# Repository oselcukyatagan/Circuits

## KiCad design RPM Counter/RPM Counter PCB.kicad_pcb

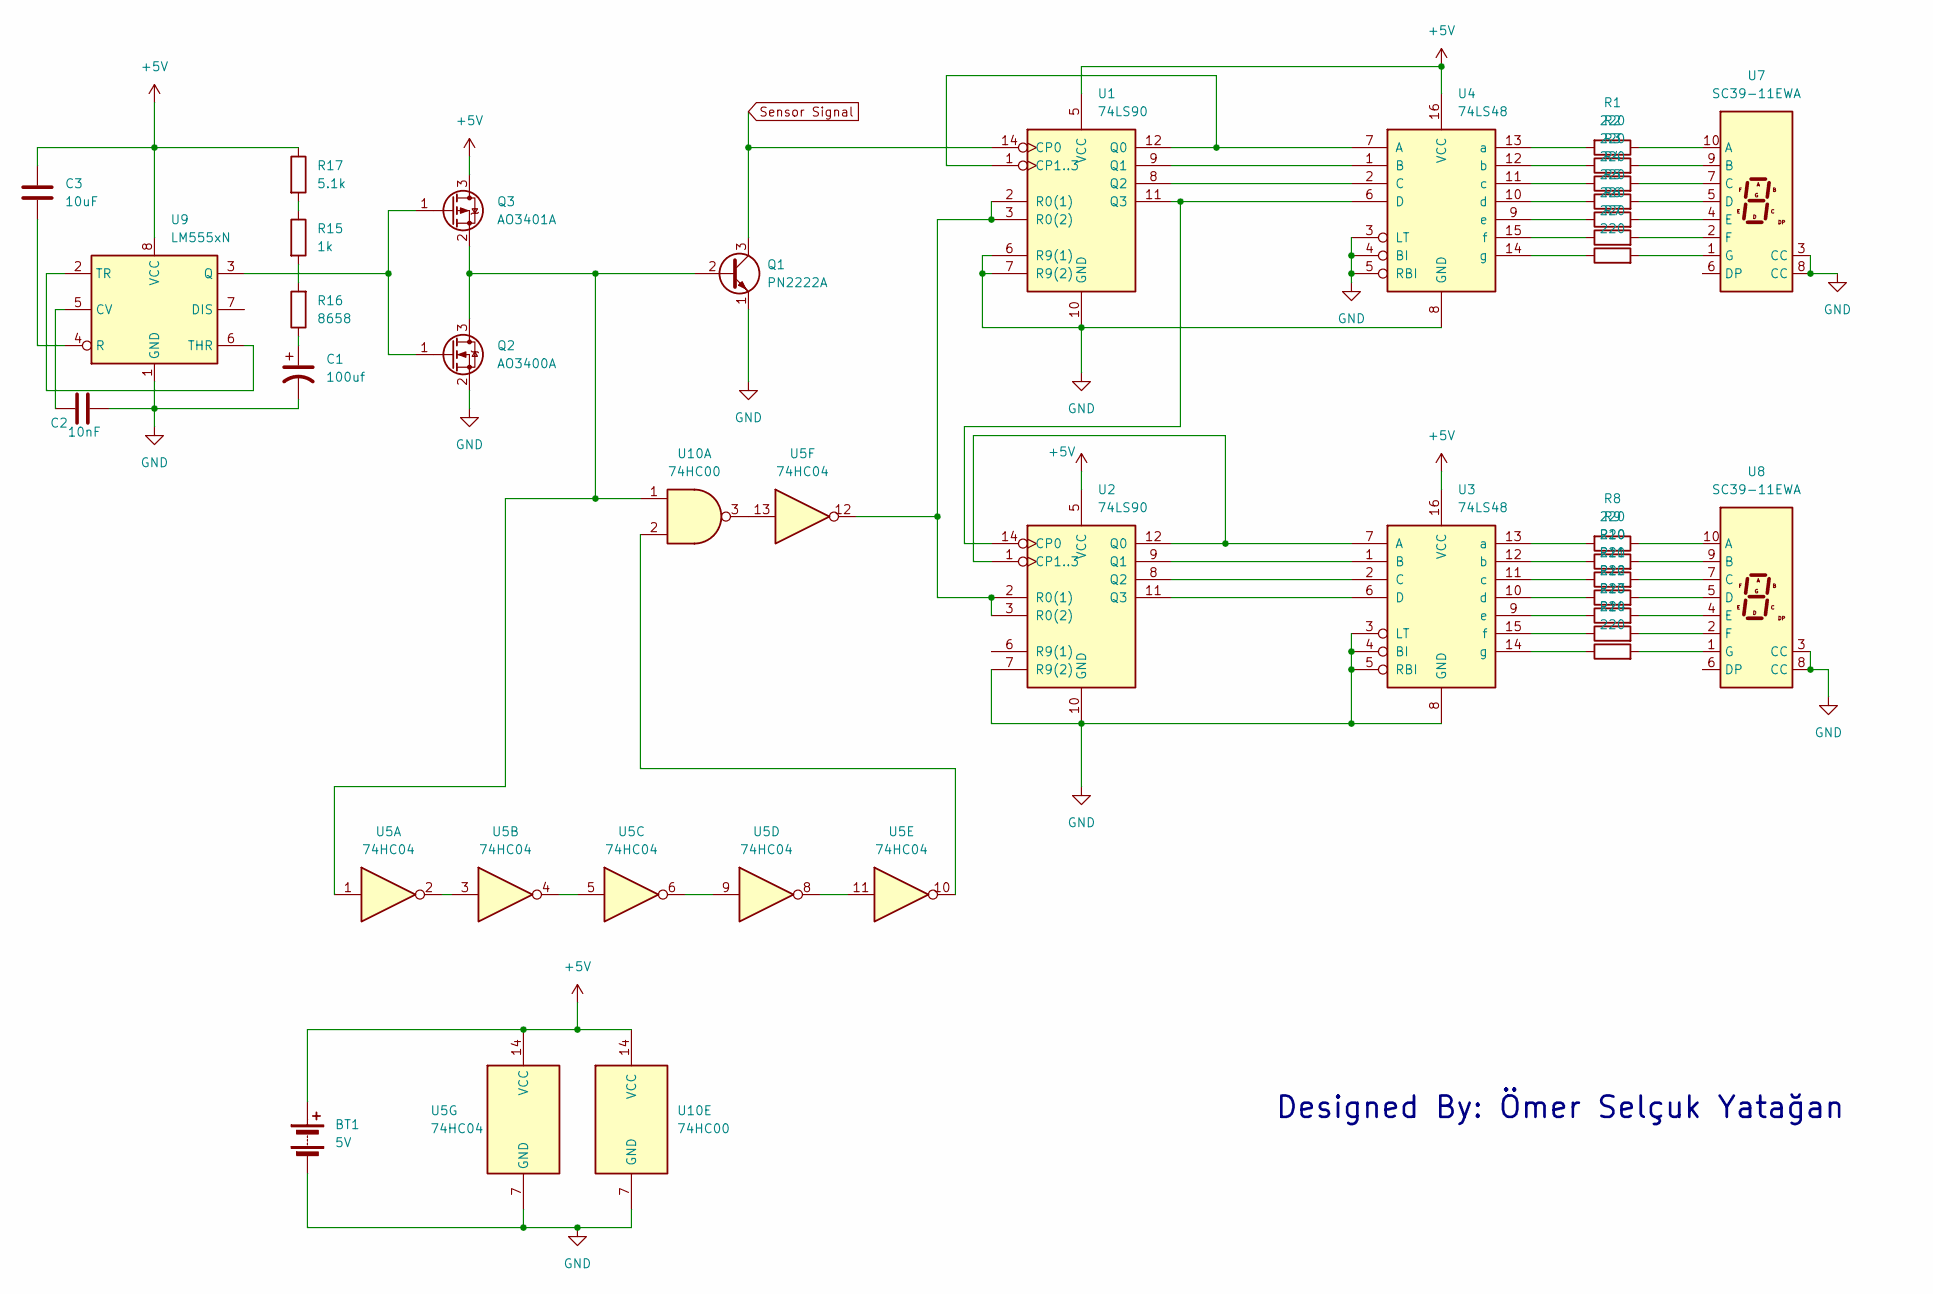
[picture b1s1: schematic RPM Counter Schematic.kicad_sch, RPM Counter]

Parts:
BT1: 5V; PinHeader_2x01_P2.54mm_Vertical
C1: 100uf; CP_Radial_D5.0mm_P2.50mm
C2: 10nF; CP_Radial_D5.0mm_P2.50mm
C3: 10uF; CP_Radial_D5.0mm_P2.50mm
Q1: PN2222A; TO-92_Inline
Q2: AO3400A; TO-92L_HandSolder
Q3: AO3401A; TO-92_HandSolder
R1, R2, R3, R4, R5, R6, R7, R8, R9, R10, R11, R12, R13, R14: 220; R_Axial_DIN0207_L6.3mm_D2.5mm_P7.62mm_Horizontal
R15: 1k; R_Axial_DIN0207_L6.3mm_D2.5mm_P7.62mm_Horizontal
R16: 8658; R_Axial_DIN0207_L6.3mm_D2.5mm_P7.62mm_Horizontal
R17: 5.1k; R_Axial_DIN0207_L6.3mm_D2.5mm_P7.62mm_Horizontal
U1, U2: 74LS90; DIP-14_W7.62mm_Socket_LongPads
U3, U4: 74LS48; DIP-16_W7.62mm_Socket_LongPads
U5: 74HC04; DIP-14_W7.62mm_Socket_LongPads
U7, U8: SC39-11EWA; Sx39-1xxxxx
U9: LM555xN; DIP-8_W7.62mm
U10: 74HC00; DIP-14_W7.62mm_Socket_LongPads

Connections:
+5V: BT1.1 (+), C3.1, Q3.3 (D), R17.1, U1.5 (VCC), U2.5 (VCC), U3.16 (VCC), U4.16 (VCC), U5.14 (VCC), U9.8 (VCC), U10.14 (VCC)
GND: BT1.2 (-), C1.2, C2.2, Q1.1 (E), Q2.2 (S), U1.6 (R9(1)), U1.7 (R9(2)), U1.10 (GND), U2.7 (R9(2)), U2.10 (GND), U3.3 (LT), U3.4 (BI), U3.5 (RBI), U3.8 (GND), U4.3 (LT), U4.4 (BI), U4.5 (RBI), U4.8 (GND), U5.7 (GND), U7.3 (CC), U7.8 (CC), U8.3 (CC), U8.8 (CC), U9.1 (GND), U10.7 (GND)
unnamed: C1.1, R16.1
unnamed: Q1.2 (B), Q2.3 (D), Q3.2 (S), U5.1, U10.1
unnamed: Q2.1 (G), Q3.1 (G), U9.3 (Q)
unnamed: R15.1, R17.2
unnamed: R15.2, R16.2
unnamed: U1.1 (CP1..3), U1.12 (Q0), U4.7 (A)
unnamed: U1.9 (Q1), U4.1 (B)
unnamed: U1.8 (Q2), U4.2 (C)
unnamed: U1.11 (Q3), U2.14 (CP0), U4.6 (D)
unnamed: U1.2 (R0(1)), U1.3 (R0(2)), U2.2 (R0(1)), U2.3 (R0(2)), U5.12
unnamed: U2.1 (CP1..3), U2.12 (Q0), U3.7 (A)
unnamed: U2.9 (Q1), U3.1 (B)
unnamed: U2.8 (Q2), U3.2 (C)
unnamed: U2.11 (Q3), U3.6 (D)
unnamed: R8.2, U3.13 (a)
unnamed: R9.1, U3.12 (b)
unnamed: R10.1, U3.11 (c)
unnamed: R11.1, U3.10 (d)
unnamed: R12.1, U3.9 (e)
unnamed: R13.1, U3.15 (f)
unnamed: R14.1, U3.14 (g)
unnamed: R1.2, U4.13 (a)
unnamed: R2.1, U4.12 (b)
unnamed: R3.1, U4.11 (c)
unnamed: R4.1, U4.10 (d)
unnamed: R5.1, U4.9 (e)
unnamed: R6.1, U4.15 (f)
unnamed: R7.1, U4.14 (g)
unnamed: U5.2, U5.3
unnamed: U5.4, U5.5
unnamed: U5.6, U5.9
unnamed: U5.8, U5.11
unnamed: R1.1, U7.10 (A)
unnamed: R2.2, U7.9 (B)
unnamed: R3.2, U7.7 (C)
unnamed: R4.2, U7.5 (D)
unnamed: R5.2, U7.4 (E)
unnamed: R6.2, U7.2 (F)
unnamed: R7.2, U7.1 (G)
unnamed: R8.1, U8.10 (A)
unnamed: R9.2, U8.9 (B)
unnamed: R10.2, U8.7 (C)
unnamed: R11.2, U8.5 (D)
unnamed: R12.2, U8.4 (E)
unnamed: R13.2, U8.2 (F)
unnamed: R14.2, U8.1 (G)
unnamed: C2.1, U9.5 (CV)
unnamed: C3.2, U9.4 (R)
unnamed: U9.2 (TR), U9.6 (THR)
unnamed: U5.10, U10.2
unnamed: U5.13, U10.3
Sensor Signal: Q1.3 (C), U1.14 (CP0)

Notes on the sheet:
Designed By: Ömer Selçuk Yatağan

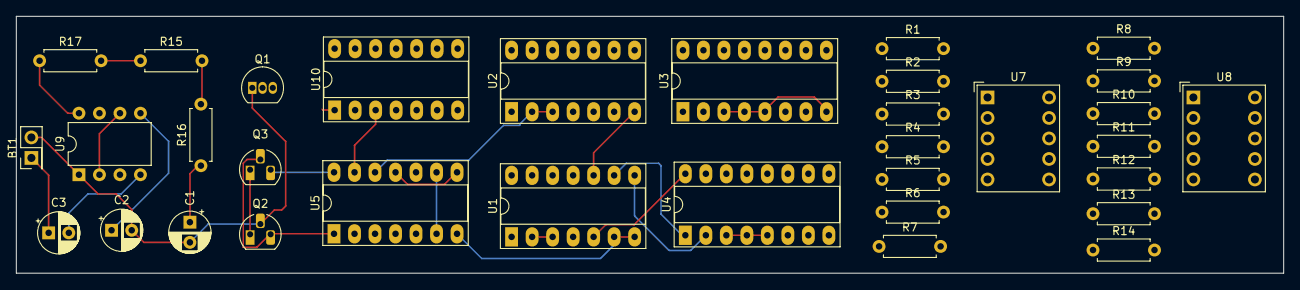
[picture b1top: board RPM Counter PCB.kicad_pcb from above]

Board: 2 copper layers, 157.0 x 31.8 mm, 33 parts (0 on the bottom side), 54 nets.

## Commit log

2024-12-22 Added LTspice simulation file.
